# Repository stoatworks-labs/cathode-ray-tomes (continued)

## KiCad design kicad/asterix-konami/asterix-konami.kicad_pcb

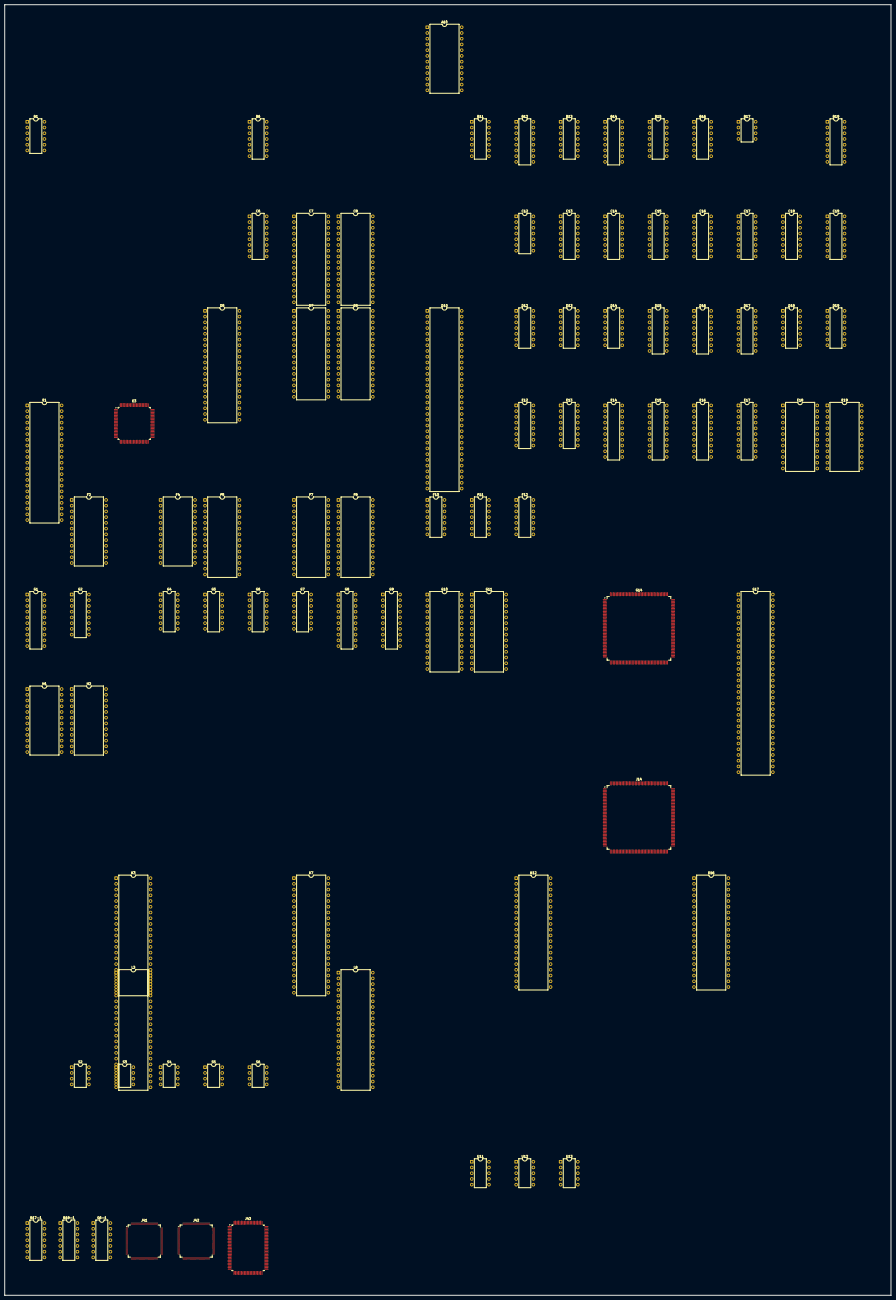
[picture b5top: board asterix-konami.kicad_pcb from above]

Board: 2 copper layers, 392.8 x 572.0 mm, 87 parts (0 on the bottom side), 556 nets, no tracks yet.

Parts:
A10: 051550; DIP-24_W15.24mm
B1: MB3722; DIP-12_W7.62mm
B6: LM324; DIP-14_W7.62mm
B11: 74LS74; DIP-14_W7.62mm
B12, B14: 74LS257; DIP-16_W7.62mm
B13: 74LS20; DIP-14_W7.62mm
B15, B16, B17-1, B18-1: 74LS07; DIP-14_W7.62mm
B17: ER5911; DIP-8_W7.62mm
B19: 74LS174; DIP-16_W7.62mm
C6: YM3012; DIP-16_W7.62mm
C7, C8: 27C010; DIP-32_W15.24mm
C12: 74LS74; DIP-14_W7.62mm
C13: 74LS139; DIP-16_W7.62mm
C14: 74LS138; DIP-16_W7.62mm
C15, C17: 74LS153; DIP-16_W7.62mm
C16: 74LS257; DIP-16_W7.62mm
C18, C19: 74LS174; DIP-16_W7.62mm
D5: Z80CPU; DIP-40_W15.24mm
D7, D8: 27C010; DIP-32_W15.24mm
D10: 68000D; DIP-64_W15.24mm
D12, D14: 74LS74; DIP-14_W7.62mm
D13: 74LS04; DIP-14_W7.62mm
D15, D17: 74LS157; DIP-16_W7.62mm
D16: 74LS257; DIP-16_W7.62mm
D18: 74LS32; DIP-14_W7.62mm
D19: 74LS164; DIP-14_W7.62mm
E1: DIP-42_W15.24mm
E3: 053260; PQFP-80_14x14mm_P0.65mm
E12: 74LS138; DIP-16_W7.62mm
E13: 74LS157; DIP-16_W7.62mm
E14, E17: 74LS245; DIP-20_W7.62mm
E15, E16: 74LS273; DIP-20_W7.62mm
E18, E19: HM6116P-3; DIP-24_W15.24mm
F2: CY7C128-45PC; DIP-24_W15.24mm
F4: YM2151; DIP-24_W15.24mm
F5: 27C512; DIP-28_W15.24mm
F7, F8: MB8464A-10W-15W; DIP-28_W15.24mm
F10: 74LS04; DIP-14_W7.62mm
F11: 74LS00; DIP-14_W7.62mm
F12: 74LS74; DIP-14_W7.62mm
G1: PAL16L8; DIP-20_W7.62mm
G2: 74LS161; DIP-16_W7.62mm
G4: 74LS04; DIP-14_W7.62mm
G5: 74LS00; DIP-14_W7.62mm
G6: 74LS74; DIP-14_W7.62mm
G6-1, G7: 74LS08; DIP-14_W7.62mm
G8, G9: 74LS245; DIP-20_W7.62mm
G10, G11: MB8464A-10W-15W; DIP-28_W15.24mm
G14: 054156; PQFP-160_28x28mm_P0.65mm
G17: DIP-64_W15.24mm
H1, H2: HM6116P-3; DIP-24_W15.24mm
J14: 054157; PQFP-160_28x28mm_P0.65mm
J41: 053245; TQFP-120_14x14mm_P0.4mm
J42: 053244; TQFP-120_14x14mm_P0.4mm
J43: 053251; PQFP-100_14x20mm_P0.65mm
K3, K7: DIP-42_W15.24mm
K12, K16: 955D05-06-07-08; DIP-40_W15.24mm
L3, L8: DIP-42_W15.24mm
S2, S3, S4, S5, S6: KONAMI_005273; DIP-8_W7.62mm
U11, U12, U13: 052535; DIP-10_W7.62mm

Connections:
/+12V: A10.19, B1.10
/ACOL0: J14.149, J43.57
/ACOL1: J14.148, J43.58
/ACOL2: J14.55, J43.59
/ACOL3: J14.56, J43.60
/APAL0: J14.127, J43.61
/APAL1: J14.126, J43.62
/APAL2: J14.125, J43.63
/AUX1: E3.23, F4.21
/BCOL0: J14.147, J43.66
/BCOL1: J14.146, J43.67
/BCOL2: J14.57, J43.68
/BCOL3: J14.58, J43.69
/BNK~CS: C14.11, C18.9, C19.9
/BNK~SCR: C14.7, J14.64
/BPAL0: J14.119, J43.70
/BPAL1: J14.118, J43.71
/BPAL2: J14.117, J43.72
/CI0: J14.154, J43.4
/CI1: J14.153, J43.5
/CI2: J14.51, J43.6
/CI3: J14.52, J43.7
/CI4: J14.142, J43.8
/CI5: J14.141, J43.9
/CI6: J14.138, J43.10
/COIN_CNT_1: A10.22, A10.23
/COIN_CNT_2: A10.20, A10.21
/CPG~CS: C14.10, J43.81
/FCOL0: J14.152, J43.47
/FCOL1: J14.151, J43.48
/FCOL2: J14.53, J43.49
/FCOL3: J14.54, J43.50
/FPAL0: J14.134, J43.51
/FPAL1: J14.133, J43.52
/FPAL2: J14.132, J43.54
/GFXROMA17: B19.15, K12.1, K16.1
/IO': B19.9, C14.14
/IO~OE: B12.15, B14.15, C14.15, C16.15, D16.15
/M3: C12.2, D14.11, G14.125
/M6: C12.3, D12.3, D12.11, D19.8, E15.11, E16.11, F12.12, G4.4, J43.41
/M12: B11.9, D10.15, G14.122, G17.56, J14.111
/MAIN_A1: C7.12, C8.12, D7.12, D8.12, D10.29, D15.2, D18.1, E3.18, F7.10, F8.10, G14.95, G17.30, J14.74, J41.25, J42.19, J43.85
/MAIN_A2: C7.11, C8.11, D7.11, D8.11, D10.30, D15.5, F7.9, F8.9, G14.96, G17.29, J14.75, J41.24, J42.18, J43.84
/MAIN_A3: C7.10, C8.10, D7.10, D8.10, D10.31, D15.11, F7.8, F8.8, G14.97, G17.28, J41.23, J42.17, J43.83
/MAIN_A4: C7.9, C8.9, D7.9, D8.9, D10.32, D15.14, F7.7, F8.7, G14.98, G17.27, J41.22, J42.15, J43.82
/MAIN_A5: C7.8, C8.8, D7.8, D8.8, D10.33, E13.2, F7.6, F8.6, G14.99, G17.24, J41.20
/MAIN_A6: C7.7, C8.7, D7.7, D8.7, D10.34, E13.5, F7.5, F8.5, G14.101, G17.23, J41.19
/MAIN_A7: C7.6, C8.6, D7.6, D8.6, D10.35, E13.11, F7.4, F8.4, G14.102, G17.22, J41.18
/MAIN_A8: C7.5, C8.5, C14.1, D7.5, D8.5, D10.36, E13.14, F7.3, F8.3, G14.103, G17.21, J41.17
/MAIN_A9: C7.27, C8.27, C14.2, D7.27, D8.27, D10.37, D17.2, F7.25, F8.25, G14.104, G17.20, J41.15
/MAIN_A10: C7.26, C8.26, C14.3, D7.26, D8.26, D10.38, D17.5, F7.24, F8.24, G14.105, G17.19, J41.14
/MAIN_A11: C7.23, C8.23, C14.4, D7.23, D8.23, D10.39, D17.11, F7.21, F8.21, G6-1.1, G7.1, G14.106, G17.17
/MAIN_A12: C7.25, C8.25, D7.25, D8.25, D10.40, F7.23, F8.23, G14.107, G17.16
/MAIN_A13: C7.4, C8.4, D7.4, D8.4, D10.41, F7.2, F8.2, G14.108, G17.15
/MAIN_A14: C7.28, C8.28, D7.28, D8.28, D10.42, F7.26, F8.26, G17.14
/MAIN_A15: C7.29, C8.29, D7.29, D8.29, D10.43, G17.13
/MAIN_A16: C7.3, C8.3, D7.3, D8.3, D10.44, G17.12
/MAIN_A17: C7.2, C8.2, C13.2, D7.2, D8.2, D10.45, G17.11
/MAIN_A18: C13.3, D10.46, G17.8
/MAIN_A19: D10.47, E12.1, G17.7
/MAIN_A20: D10.48, E12.2, G17.6
/MAIN_A21: D10.50, G17.5
/MAIN_A22: C13.14, D10.51, D13.11, E12.3, G17.4
/MAIN_A23: C13.13, D10.52, E12.4, G17.3
/MAIN_D0: B12.4, B19.3, C19.3, D7.13, D8.13, D10.5, E3.8, E17.2, F8.11, G8.18, G14.76, G17.31, J14.76, J42.29, J43.80
/MAIN_D1: B12.7, B19.4, C19.4, D7.14, D8.14, D10.4, E3.9, E17.3, F8.12, G8.17, G14.77, G17.32, J14.77, J42.28, J43.79
/MAIN_D2: B12.9, B19.6, C19.6, D7.15, D8.15, D10.3, E3.10, E17.4, F8.13, G8.16, G14.78, G17.33, J14.78, J42.27, J43.77
/MAIN_D3: B12.12, B19.11, C19.11, D7.17, D8.17, D10.2, E3.11, E17.5, F8.15, G8.15, G14.79, G17.35, J14.79, J42.26, J43.76
/MAIN_D4: B14.4, B19.13, C19.13, D7.18, D8.18, D10.1, E3.13, E17.6, F8.16, G8.14, G14.82, G17.36, J14.82, J42.25, J43.75
/MAIN_D5: B14.7, B19.14, C19.14, D7.19, D8.19, D10.64, E3.14, E17.7, F8.17, G8.13, G14.83, G17.37, J14.83, J42.24, J43.74
/MAIN_D6: B14.9, C18.3, D7.20, D8.20, D10.63, E3.15, E17.8, F8.18, G8.12, G14.84, G17.38, J14.84, J42.23
/MAIN_D7: B14.12, C18.4, D7.21, D8.21, D10.62, E3.16, E17.9, F8.19, G8.11, G14.85, G17.39, J14.85, J42.22
/MAIN_D8: C7.13, C8.13, C16.4, C18.6, D10.61, E14.2, F7.11, G9.18, G14.86, G17.40, J14.86
/MAIN_D9: C7.14, C8.14, C16.7, C18.11, D10.60, E14.3, F7.12, G9.17, G14.87, G17.43, J14.87
/MAIN_D10: C7.15, C8.15, C16.9, C18.13, D10.59, E14.4, F7.13, G9.16, G14.88, G17.44, J14.88
/MAIN_D11: C7.17, C8.17, C16.12, C18.14, D10.58, E14.5, F7.15, G9.15, G14.89, G17.45, J14.89
/MAIN_D12: C7.18, C8.18, D10.57, D16.4, E14.6, F7.16, G9.14, G14.91, G17.46, J14.91
/MAIN_D13: C7.19, C8.19, D10.56, D16.7, E14.7, F7.17, G9.13, G14.92, G17.47, J14.92
/MAIN_D14: C7.20, C8.20, D10.55, D16.9, E14.8, F7.18, G9.12, G14.93, G17.48, J14.93
/MAIN_D15: C7.21, C8.21, D10.54, D16.12, E14.9, F7.19, G9.11, G14.94, G17.49, J14.94
/MRESET: A10.1, C14.9
/M~DS: D13.1, G6-1.6, J42.14
/M~RD: C7.22, C8.22, D7.22, D8.22, D17.14, E14.1, E17.1, F7.22, F8.22, F11.1, F11.13, G4.10, J41.13, J42.20
/OBJ~CE: F11.6, G5.1
/OBJ~CS: D18.5, E12.12, F11.4
/OBJ~RD: E12.11, F11.5, G7.5
/OBJ~SET: E12.9, J41.6, J42.13
/OCOL0: J42.120, J43.30
/OCOL1: J42.119, J43.31
/OCOL2: J42.118, J43.32
/OCOL3: J42.117, J43.33
/OCOL4: J42.116, J43.34
/OCOL5: J42.115, J43.35
/OCOL6: J42.114, J43.36
/OCOL7: J42.113, J43.37
/OCOL8: J42.112, J43.38
/PAL~CS: D15.1, D17.1, D18.10, D18.13, E12.10, E13.1, E14.19, E17.19
/PCMCLK: E3.21, F4.24, G2.12
/PCM~CS: E3.72, G1.19
/PR13: J42.110, J43.25
/PR14: J42.109, J43.27
/R/~W: D10.9, D18.4, E3.19, G4.11
/SDI0: J42.108, J43.95
/SH1: C6.6, E3.26, G6.11
/SND_A0: D5.30, E3.70, F2.8, F4.4, F5.10
/SND_A1: D5.31, E3.69, F2.7, F5.9
/SND_A2: D5.32, E3.68, F2.6, F5.8
/SND_A3: D5.33, E3.67, F2.5, F5.7
/SND_A4: D5.34, E3.66, F2.4, F5.6
/SND_A5: D5.35, E3.65, F2.3, F5.5
/SND_A6: D5.36, F2.2, F5.4
/SND_A7: D5.37, F2.1, F5.3
/SND_A8: D5.38, F2.23, F5.25
/SND_A9: D5.39, F2.22, F5.24, G1.14
/SND_A10: D5.40, F2.19, F5.21, G1.13
/SND_A11: D5.1, F5.23, G1.11
/SND_A12: D5.2, F5.2, G1.9
/SND_A13: D5.3, F5.26, G1.8
/SND_A14: D5.4, F5.27, G1.7
/SND_A15: D5.5, F5.1, G1.6
/SND_D0: D5.14, E3.5, F2.9, F4.10, F5.11
/SND_D1: D5.15, E3.4, F2.10, F4.12, F5.12
/SND_D2: D5.12, E3.3, F2.11, F4.13, F5.13
/SND_D3: D5.8, E3.2, F2.13, F4.14, F5.15
/SND_D4: D5.7, E3.1, F2.14, F4.15, F5.16
/SND_D5: D5.9, E3.80, F2.15, F4.16, F5.17
/SND_D6: D5.10, E3.79, F2.16, F4.17, F5.18
/SND_D7: D5.13, E3.78, F2.17, F4.18, F5.19
/STBI: E3.22, F4.20
/S~RD: D5.21, F2.20, F4.6, F10.13, G1.4
/TMG2TD0: G14.64, J14.62
/TMG2TD1: G14.109, J14.68
/TMG2TD2: G14.124, J14.69
/TMG2TD3: G14.126, J14.72
/TMG2TD4: G14.127, J14.73
/TMG2TD5: G14.128, J14.95
/TMG2TD6: G14.129, J14.98
/TMG2TD7: D13.4, G14.62, J14.112
/colmix/CO0: D15.3, J43.19
/colmix/CO1: D15.6, J43.18
/colmix/CO2: D15.10, J43.17
/colmix/CO3: D15.13, J43.16
/colmix/CO4: E13.3, J43.14
/colmix/CO5: E13.6, J43.13
/colmix/CO6: E13.10, J43.12
/colmix/CO7: E13.13, J43.11
/colmix/CO8: D17.3, J43.93
/colmix/CO9: D17.6, J43.92
/colmix/CO10: D17.10, J43.91
/colmix/MCO0: D15.4, E18.8, E19.8
/colmix/MCO1: D15.7, E18.7, E19.7
/colmix/MCO2: D15.9, E18.6, E19.6
/colmix/MCO3: D15.12, E18.5, E19.5
/colmix/MCO4: E13.4, E18.4, E19.4
/colmix/MCO5: E13.7, E18.3, E19.3
/colmix/MCO6: E13.9, E18.2, E19.2
/colmix/MCO7: E13.12, E18.1, E19.1
/colmix/MCO8: D17.4, E18.23, E19.23
/colmix/MCO9: D17.7, E18.22, E19.22
/colmix/MCO10: D17.9, E18.19, E19.19
/colmix/MCO~OE: D17.12, E18.20, E19.20
/colmix/MCO~WRH: D18.8, E19.21
/colmix/MCO~WRL: D18.11, E18.21
/colmix/RGB0: E15.4, E17.18, E18.9
/colmix/RGB1: E15.7, E17.17, E18.10
/colmix/RGB2: E15.8, E17.16, E18.11
/colmix/RGB3: E15.13, E17.15, E18.13
/colmix/RGB4: E15.14, E17.14, E18.14
/colmix/RGB5: E15.17, E17.13, E18.15
/colmix/RGB6: E15.18, E17.12, E18.16
/colmix/RGB7: E16.3, E17.11, E18.17
/colmix/RGB8: E14.18, E16.4, E19.9
/colmix/RGB9: E14.17, E16.7, E19.10
/colmix/RGB10: E14.16, E16.8, E19.11
/colmix/RGB11: E14.15, E16.13, E19.13
/colmix/RGB12: E14.14, E16.14, E19.14
/colmix/RGB13: E14.13, E16.17, E19.15
/colmix/RGB14: E14.12, E16.18, E19.16
/colmix/RGB15: E14.11, E19.17
/colmix/SDO1: D13.5, J43.86
/colmix/rgb/B10: B15.3, E16.9
/colmix/rgb/B11: B17-1.9, E16.12
/colmix/rgb/B12: B15.5, E16.15
/colmix/rgb/B13: B17-1.11, E16.16
/colmix/rgb/B14: B18-1.9, E16.19
/colmix/rgb/G5: B16.3, E15.16
/colmix/rgb/G6: B17-1.13, E15.19
/colmix/rgb/G7: B16.5, E16.2
/colmix/rgb/G8: B17-1.3, E16.5
/colmix/rgb/G9: B15.1, E16.6
/colmix/rgb/R0: B16.9, E15.5
/colmix/rgb/R1: B15.9, E15.6
/colmix/rgb/R2: B16.11, E15.9
/colmix/rgb/R3: B15.11, E15.12
/colmix/rgb/R4: B16.13, E15.15
/colmix/rgb/~SHADOW: B15.13, B18-1.5, B18-1.13, E15.2
/io_cabinet/I1P_BTN_1: B14.2, S5.3
/io_cabinet/I1P_BTN_2: B14.5, S6.7
/io_cabinet/I1P_BTN_3: B14.11, S6.3
/io_cabinet/I1P_DOWN: B12.14, S4.7
/io_cabinet/I1P_LEFT: B12.2, S4.3
/io_cabinet/I1P_RIGHT: B12.5, S5.7
/io_cabinet/I1P_START: B14.14, S3.7
/io_cabinet/I1P_UP: B12.11, S3.3
/io_cabinet/I2P_BTN_1: B14.3, S5.1
/io_cabinet/I2P_BTN_2: B14.6, S6.5
/io_cabinet/I2P_BTN_3: B14.10, S6.1
/io_cabinet/I2P_DOWN: B12.13, S4.5
/io_cabinet/I2P_LEFT: B12.3, S4.1
/io_cabinet/I2P_RIGHT: B12.6, S5.5
/io_cabinet/I2P_START: B14.13, S3.5
/io_cabinet/I2P_UP: B12.10, S3.1
/io_cabinet/ICOIN_1: C16.2, S2.3
/io_cabinet/ICOIN_2: C16.5, S2.1
/io_cabinet/ISERVICE1: C16.11, S2.7
/io_cabinet/ITEST SW1: C16.10, S2.5
/io_cabinet/~M12: B11.8, B11.12, C12.11, F12.2
/main/AS: B13.9, D12.4, D12.10, D14.4, D14.10, G4.2
/main/~AS: C13.15, D10.6, E12.5, G4.1, G17.1
/main/~BGACK: D10.12, G17.53
/main/~BG: D10.11, G17.52
/main/~BR: D10.13, G17.51
/main/~CS1: E12.13, F7.20, F8.20
/main/~DTACK: D10.10, D13.12, G17.61
/main/~IO: C14.5, E12.7, F10.1
/main/~OE1: C8.24, D8.24, E12.15
/main/~OE2: C7.24, D7.24, E12.14
/objects/AR0: J41.119, J42.30
/objects/AR1: J41.118, J42.32
/objects/AR2: J41.117, J42.33
/objects/AROK: J41.116, J42.34
/objects/BR0: J41.115, J42.35
/objects/BR1: J41.114, J42.36
/objects/BR2: J41.113, J42.37
/objects/BROK: J41.112, J42.38
/objects/CLAT: J41.86, J42.64
/objects/CPU: F10.10, G5.2, G7.2
/objects/HP0: J41.96, J42.54
/objects/HP1: J41.97, J42.53
/objects/HP2: J41.98, J42.52
/objects/HP3: J41.99, J42.50
/objects/HP4: J41.100, J42.49
/objects/HP5: J41.102, J42.48
/objects/HP6: J41.103, J42.47
/objects/HP7: J41.104, J42.45
/objects/HP8: J41.105, J42.44
/objects/HP9: J41.107, J42.43
/objects/HRFP: J41.110, J42.39
/objects/MA11: G7.3, H1.19, H2.19
/objects/MAIN_D'0: C17.2, C17.6, C17.14, C19.2, J41.64, J41.65, J41.66, J41.67, J41.68, J41.69, J41.70, J41.85, K3.10, K3.33, K3.34, K3.35, K3.36, K3.37, K7.10, K7.33, K7.34, K7.35, K7.36, K7.37, L3.10, L3.33, L3.34, L3.35, L3.36, L3.37, L8.10, L8.33, L8.34, L8.35, L8.36, L8.37
/objects/MAIN_D'1: C17.10, C19.5, J41.84, K3.9, K7.9, L3.9, L8.9
/objects/MAIN_D'2: C15.6, C19.7, J41.83, K3.8, K7.8, L3.8, L8.8
/objects/MAIN_D'3: C17.5, C19.10, J41.82, K3.7, K7.7, L3.7, L8.7
/objects/MAIN_D'4: C17.11, C19.12, J41.80, K3.6, K7.6, L3.6, L8.6
/objects/MAIN_D'5: C15.5, C19.15, J41.79, K3.5, K7.5, L3.5, L8.5
/objects/MAIN_D'6: C17.4, C18.2, J41.78, K3.4, K7.4, L3.4, L8.4
/objects/MAIN_D'7: C17.12, C18.5, J41.77, K3.3, K7.3, L3.3, L8.3
/objects/MAIN_D'8: C15.4, C18.7, J41.75, K3.41, K7.41, L3.41, L8.41
/objects/MAIN_D'9: C17.3, C18.10, J41.74, K3.40, K7.40, L3.40, L8.40
/objects/MAIN_D'10: C17.13, C18.12, J41.73, K3.39, K7.39, L3.39, L8.39
/objects/MAIN_D'11: C15.3, C18.15, J41.72, K3.38, K7.38, L3.38, L8.38
/objects/MAIN_D'[11..0]: C15.2, C15.14
/objects/OBJROMD0: J42.100, K7.14, L3.14
/objects/OBJROMD1: J42.99, K7.16, L3.16
/objects/OBJROMD2: J42.98, K7.18, L3.18
/objects/OBJROMD3: J42.97, K7.20, L3.20
/objects/OBJROMD4: J42.96, K7.23, L3.23
/objects/OBJROMD5: J42.95, K7.25, L3.25
/objects/OBJROMD6: J42.94, K7.27, L3.27
/objects/OBJROMD7: J42.93, K7.29, L3.29
/objects/OBJROMD8: J42.92, K7.15, L3.15
/objects/OBJROMD9: J42.90, K7.17, L3.17
/objects/OBJROMD10: J42.89, K7.19, L3.19
/objects/OBJROMD11: J42.88, K7.21, L3.21
/objects/OBJROMD12: J42.87, K7.24, L3.24
/objects/OBJROMD13: J42.86, K7.26, L3.26
/objects/OBJROMD14: J42.85, K7.28, L3.28
/objects/OBJROMD15: J42.84, K7.30, L3.30
/objects/OBJROMD16: J42.83, K3.14, L8.14
/objects/OBJROMD17: J42.82, K3.16, L8.16
/objects/OBJROMD18: J42.80, K3.18, L8.18
/objects/OBJROMD19: J42.79, K3.20, L8.20
/objects/OBJROMD20: J42.78, K3.23, L8.23
/objects/OBJROMD21: J42.77, K3.25, L8.25
/objects/OBJROMD22: J42.75, K3.27, L8.27
/objects/OBJROMD23: J42.74, K3.29, L8.29
/objects/OBJROMD24: J42.73, K3.15, L8.15
/objects/OBJROMD25: J42.72, K3.17, L8.17
/objects/OBJROMD26: J42.70, K3.19, L8.19
/objects/OBJROMD27: J42.69, K3.21, L8.21
/objects/OBJROMD28: J42.68, K3.24, L8.24
/objects/OBJROMD29: J42.67, K3.26, L8.26
/objects/OBJROMD30: J42.66, K3.28, L8.28
/objects/OBJROMD31: J42.65, K3.30, L8.30
/objects/PL0: J41.87, J42.63
/objects/PL1: J41.88, J42.62
/objects/PL2: J41.89, J42.60
/objects/PL3: J41.90, J42.59
/objects/PL4: J41.92, J42.58
/objects/PL5: J41.93, J42.57
/objects/PL6: J41.94, J42.56
/objects/RA1: H1.8, H2.8, J41.52
/objects/RA2: H1.7, H2.7, J41.53
/objects/RA3: H1.6, H2.6, J41.54
/objects/RA4: H1.5, H2.5, J41.55
/objects/RA5: H1.4, H2.4, J41.56
/objects/RA6: H1.3, H2.3, J41.57
/objects/RA7: H1.2, H2.2, J41.58
/objects/RA8: H1.1, H2.1, J41.59
/objects/RA9: H1.23, H2.23, J41.62
/objects/RA10: H1.22, H2.22, J41.63
/objects/RD0: G8.2, H2.9, J41.45
/objects/RD1: G8.3, H2.10, J41.44
/objects/RD2: G8.4, H2.11, J41.43
/objects/RD3: G8.5, H2.13, J41.42
/objects/RD4: G8.6, H2.14, J41.40
/objects/RD5: G8.7, H2.15, J41.39
/objects/RD6: G8.8, H2.16, J41.38
/objects/RD7: G8.9, H2.17, J41.37
/objects/RD8: G9.2, H1.9, J41.35
/objects/RD9: G9.3, H1.10, J41.34
/objects/RD10: G9.4, H1.11, J41.33
/objects/RD11: G9.5, H1.13, J41.32
/objects/RD12: G9.6, H1.14, J41.30
/objects/RD13: G9.7, H1.15, J41.29
/objects/RD14: G9.8, H1.16, J41.28
/objects/RD15: G9.9, H1.17, J41.27
/objects/R~OE: H1.20, H2.20, J41.49
/objects/SHADOW: J41.95, J42.55
/objects/~HIT: J41.108, J42.42
/objects/~WE1: H2.21, J41.48
/objects/~WE2: H1.21, J41.47
/objects/~ZLD: J41.109, J42.40
/pcm/RA0: E1.30, E3.39
/pcm/RA1: E1.10, E3.40
/pcm/RA2: E1.9, E3.41
/pcm/RA3: E1.8, E3.42
/pcm/RA4: E1.7, E3.44
/pcm/RA5: E1.6, E3.45
/pcm/RA6: E1.5, E3.46
/pcm/RA7: E1.4, E3.47
/pcm/RA8: E1.3, E3.48
/pcm/RA9: E1.41, E3.49
/pcm/RA10: E1.40, E3.50
/pcm/RA11: E1.39, E3.51
/pcm/RA12: E1.38, E3.53
/pcm/RA13: E1.37, E3.54
/pcm/RA14: E1.36, E3.55
/pcm/RA15: E1.35, E3.56
/pcm/RA16: E1.34, E3.57
/pcm/RA17: E1.33, E3.58
/pcm/RA18: E1.2, E3.59
/pcm/RA19: E1.1, E3.60
/pcm/RA20: E1.42, E3.62
/pcm/RD0: E1.14, E3.29
/pcm/RD1: E1.16, E3.30
/pcm/RD2: E1.18, E3.31
/pcm/RD3: E1.20, E3.32
/pcm/RD4: E1.23, E3.35
/pcm/RD5: E1.25, E3.36
/pcm/RD6: E1.27, E3.37
/pcm/RD7: E1.29, E3.38
/pcm/SH2: C6.5, E3.27
/pcm/SY: C6.2, E3.25
/scroll/GFXROMA0: G14.159, K12.9, K16.9
/scroll/GFXROMA1: G14.158, K12.8, K16.8
/scroll/GFXROMA2: G14.157, K12.7, K16.7
/scroll/GFXROMA3: G14.156, K12.6, K16.6
/scroll/GFXROMA4: G14.155, K12.5, K16.5
/scroll/GFXROMA5: G14.154, K12.4, K16.4
/scroll/GFXROMA6: G14.153, K12.3, K16.3
/scroll/GFXROMA7: G14.152, K12.2, K16.2
/scroll/GFXROMA8: G14.151, K12.40, K16.40
/scroll/GFXROMA9: G14.149, K12.39, K16.39
/scroll/GFXROMA10: G14.148, K12.38, K16.38
/scroll/GFXROMA11: G14.134, K12.37, K16.37
/scroll/GFXROMA12: G14.133, K12.36, K16.36
/scroll/GFXROMA13: G14.137, K12.35, K16.35
/scroll/GFXROMA14: G14.132, K12.34, K16.34
/scroll/GFXROMA15: G14.131, K12.33, K16.33
/scroll/GFXROMA16: G14.136, K12.32, K16.32
/scroll/GFXROMD0: J14.44, K12.13
/scroll/GFXROMD1: J14.45, K12.15
/scroll/GFXROMD2: J14.46, J14.48, K12.17
/scroll/GFXROMD3: J14.47, J14.49, K12.19
/scroll/GFXROMD4: J14.36, K12.22
/scroll/GFXROMD5: J14.37, K12.24
/scroll/GFXROMD6: J14.38, J14.42, K12.26
/scroll/GFXROMD7: J14.39, J14.43, K12.28
/scroll/GFXROMD8: J14.29, K12.14
/scroll/GFXROMD9: J14.31, K12.16
/scroll/GFXROMD10: J14.32, J14.35, K12.18
/scroll/GFXROMD11: J14.33, J14.34, K12.20
/scroll/GFXROMD12: J14.23, K12.23
/scroll/GFXROMD13: J14.24, K12.25
/scroll/GFXROMD14: J14.25, J14.27, K12.27
/scroll/GFXROMD15: J14.26, J14.28, K12.29
/scroll/GFXROMD16: J14.16, K16.13
/scroll/GFXROMD17: J14.17, K16.15
/scroll/GFXROMD18: J14.18, J14.21, K16.17
/scroll/GFXROMD19: J14.19, J14.22, K16.19
/scroll/GFXROMD20: J14.9, K16.22
/scroll/GFXROMD21: J14.11, K16.24
/scroll/GFXROMD22: J14.12, J14.14, K16.26
/scroll/GFXROMD23: J14.13, J14.15, K16.28
/scroll/GFXROMD24: J14.3, K16.14
/scroll/GFXROMD25: J14.4, K16.16
/scroll/GFXROMD26: J14.5, J14.7, K16.18
/scroll/GFXROMD27: J14.6, J14.8, K16.20
/scroll/GFXROMD28: J14.155, K16.23
/scroll/GFXROMD29: J14.156, K16.25
/scroll/GFXROMD30: J14.157, K16.27
/scroll/GFXROMD31: J14.2, J14.158, K16.29
/scroll/SCRAMA0: G10.10, G11.10, G14.28
/scroll/SCRAMA1: G10.9, G11.9, G14.29
/scroll/SCRAMA2: G10.8, G11.8, G14.31
/scroll/SCRAMA3: G10.7, G11.7, G14.32
/scroll/SCRAMA4: G10.6, G11.6, G14.33
/scroll/SCRAMA5: G10.5, G11.5, G14.34
/scroll/SCRAMA6: G10.4, G11.4, G14.35
/scroll/SCRAMA7: G10.3, G11.3, G14.36
/scroll/SCRAMA8: G10.25, G11.25, G14.37
/scroll/SCRAMA9: G10.24, G11.24, G14.38
/scroll/SCRAMA10: G10.21, G11.21, G14.39
/scroll/SCRAMA11: G10.23, G11.23, G14.42
/scroll/SCRAMA12: G10.2, G11.2, G14.45
/scroll/VD0: G11.11, G14.9
/scroll/VD1: G11.12, G14.8
/scroll/VD2: G11.13, G14.7
/scroll/VD3: G11.15, G14.6
/scroll/VD4: G11.16, G14.5
/scroll/VD5: G11.17, G14.4
/scroll/VD6: G11.18, G14.3
/scroll/VD7: G11.19, G14.2
/scroll/VD8: G10.11, G14.27
/scroll/VD9: G10.12, G14.26
/scroll/VD10: G10.13, G14.25
/scroll/VD11: G10.15, G14.24
/scroll/VD12: G10.16, G14.23
/scroll/VD13: G10.17, G14.22
/scroll/VD14: G10.18, G14.21
/scroll/VD15: G10.19, G14.19
/scroll/~M6: G4.3, G14.111
/scroll/~RCS1: G11.20, G14.52
/scroll/~RCS2: G10.20, G14.48
/scroll/~ROE1: G11.22, G14.53
/scroll/~ROE2: G10.22, G14.49
/scroll/~RWE1: G11.27, G14.54
/scroll/~RWE2: G10.27, G14.51
/sound/ROM~OE: F5.22, G1.16
/sound/SRAM~CE: F2.18, G1.17
/sound/S~IORQ: D5.20, G6-1.12
/sound/S~MREQ: D5.19, G1.2
/sound/S~WR: D5.22, F2.21, F4.5, G1.5
/sound/~M1: D5.27, G1.3
/sound/~NMISET: G1.12, G6.10
/sound/~RFSH: D5.28, G1.1
/sound/~WSET: B11.4, G1.15
/~CLKTMG: D14.5, D14.12, G14.112
/~CLKTMG~M6: F12.9, J41.10, J42.10
/~CLKTMG~M12: F12.5, J41.12, J42.12
/~CPU: C16.13, F10.11, J41.26
/~HBLANK: D19.2, G14.116
/~HSYNC: G6-1.10, G14.114, J41.4, J42.8
/~IPL0: D10.25, D16.6, G17.60
/~IPL2: D10.23, G14.72
/~LDS: D10.8, F10.5, G6-1.5, G17.63, J14.96, J41.9
/~MCS: C14.13, E3.17
/~RESET: G7.4, G17.64
/~SOUND: C14.12, G6.3
/~SYSRES: B18-1.3, B18-1.11, C6.7, C12.9, D5.26, D19.9, E3.75, F4.3, G6.13, G6-1.13, G14.71, G17.59, J14.109, J41.3, J42.3
/~UDS: D10.7, F10.3, G6-1.4, G17.62, J14.97, J41.8
/~VBLANK: D16.3, D19.1, G14.117
/~VSYNC: G6-1.9, G14.115, J41.5, J42.9
/~WEH: D18.9, F7.27, F11.11
/~WEL: D18.12, F8.27, F11.3
GND: C7.16, C8.16, D7.16, D8.16, D10.16, D10.53, F5.14, F5.20, G1.10
unnamed: A10.15, B19.10
unnamed: A10.16, B19.12
unnamed: A10.10, C12.12, C12.13
unnamed: B6.3, C6.9
unnamed: B6.1, B6.2
unnamed: B6.5, C6.15
unnamed: B6.6, C6.14
unnamed: B6.10, C6.12
unnamed: B6.8, B6.9
unnamed: B6.12, C6.10
unnamed: B6.13, B6.14
unnamed: B11.3, D5.6, G2.13
unnamed: B11.2, B11.6
unnamed: B11.11, F12.3, F12.11
unnamed: B12.1, B14.1, C16.1, D16.1, D18.3
unnamed: B13.6, D13.13
unnamed: B16.1, G6-1.8
unnamed: B17.2, B19.7
unnamed: B17.1, B19.5
unnamed: B17.3, B19.2
unnamed: B17.4, C16.3
unnamed: B17.7, C16.6
unnamed: B6.7, C6.13
unnamed: C12.6, D14.3
unnamed: C13.1, C13.11
unnamed: C13.4, D14.2
unnamed: C13.5, D12.12, D13.3
unnamed: B13.2, C13.6
unnamed: B13.4, C13.12
unnamed: C14.6, D13.2, G6-1.2
unnamed: C15.7, F10.9
unnamed: C17.7, K3.2, K7.2, L3.2, L8.2
unnamed: C17.9, K3.1, K7.1, L3.1, L8.1
unnamed: D5.16, G6.6
unnamed: D5.17, G6.9
unnamed: B13.10, D10.28
unnamed: B13.12, D10.27
unnamed: B13.13, D10.26
unnamed: B18-1.4, D10.17
unnamed: B18-1.10, D10.18
unnamed: B13.8, D10.21
unnamed: D12.2, D12.9
unnamed: B13.1, D12.5
unnamed: B13.5, D14.9
unnamed: B17-1.1, B17-1.5, B18-1.1, D19.3
unnamed: E3.71, F10.12
unnamed: D13.10, E12.6
unnamed: D13.6, E15.3
unnamed: F4.7, G1.18
unnamed: F10.2, F11.10
unnamed: F10.4, F11.12
unnamed: F10.6, F11.2
unnamed: F11.9, G6-1.3
unnamed: G6.1, G6-1.11
unnamed: G7.6, G8.1, G9.1
unnamed: G5.3, G8.19, G9.19
unnamed: F11.8, G17.54
unnamed: D18.6, J41.7
unnamed: F10.8, L3.13
unnamed: B18-1.2, U11.7
unnamed: B15.4, U11.6
unnamed: B17-1.8, U11.5
unnamed: B15.6, U11.4
unnamed: B17-1.10, U11.3
unnamed: B18-1.8, U11.2
unnamed: B17-1.6, U12.7
unnamed: B16.4, U12.6
unnamed: B17-1.12, U12.5
unnamed: B16.6, U12.4
unnamed: B17-1.4, U12.3
unnamed: B15.2, U12.2
unnamed: B17-1.2, U13.7
unnamed: B16.8, U13.6
unnamed: B15.8, U13.5
unnamed: B16.10, U13.4
unnamed: B15.10, U13.3
unnamed: B16.12, U13.2
VCC: A10.9, B6.4, B11.1, B11.10, B11.13, B11.14, B13.14, B15.14, B16.14, B17.8, B17-1.14, B18-1.14, B19.1, C6.1, C7.1, C7.31, C7.32, C8.1, C8.31, C8.32, C12.1, C12.4, C12.10, C12.14, C13.16, C16.14, C18.1, C19.1, D5.11, D7.1, D7.31, D7.32, D8.1, D8.31, D8.32, D10.14, D10.24, D10.49, D12.1, D12.13, D12.14, D13.14, D14.1, D14.13, D14.14, D16.2, D16.5, D16.10, D16.11, D16.13, D16.14, D18.14, D19.14, E1.22, E1.31, E3.20, E3.33, E3.73, E15.1, E16.1, E18.24, E19.24, F2.24, F4.22, F5.28, F7.28, F8.28, F10.14, F11.14, F12.1, F12.4, F12.10, F12.13, F12.14, G1.20, G2.1, G2.7, G2.9, G2.10, G4.14, G5.14, G6.2, G6.4, G6.14, G6-1.14, G7.14, G10.26, G10.28, G11.26, G11.28, G14.20, G14.40, G14.60, G14.80, G14.100, G14.118, G14.119, G14.120, G14.140, G14.160, G17.9, G17.26, G17.41, G17.58, H1.24, H2.24, J14.20, J14.40, J14.60, J14.65, J14.66, J14.67, J14.71, J14.80, J14.100, J14.106, J14.107, J14.108, J14.113, J14.116, J14.120, J14.122, J14.123, J14.124, J14.128, J14.129, J14.131, J14.135, J14.140, J14.159, J14.160, J41.16, J41.46, J41.60, J41.76, J41.106, J41.120, J42.16, J42.46, J42.76, J42.106, J43.1, J43.2, J43.3, J43.28, J43.29, J43.39, J43.42, J43.43, J43.44, J43.45, J43.46, J43.53, J43.78, J43.97, J43.98, J43.99, J43.100, K3.22, K3.31, K3.32, K7.22, K7.31, K7.32, K12.21, K12.31, K16.21, K16.31, L3.22, L3.31, L3.32, L8.22, L8.31, L8.32, U11.1, U12.1, U13.1
VSS: A10.13, A10.14, B1.6, B1.7, B6.11, B11.7, B13.7, B15.7, B16.7, B17.5, B17.6, B17-1.7, B18-1.7, C6.3, C6.8, C6.16, C12.7, C13.8, C15.1, C15.10, C15.11, C15.12, C15.13, C15.15, C17.1, C17.15, D5.29, D12.7, D13.7, D14.7, D15.15, D17.13, D17.15, D18.2, D18.7, D19.7, E1.11, E1.12, E1.13, E1.32, E3.6, E3.12, E3.24, E3.34, E3.43, E3.52, E3.61, E3.74, E13.15, E18.12, E18.18, E19.12, E19.18, F2.12, F4.1, F4.11, F7.14, F8.14, F10.7, F11.7, F12.7, G2.3, G2.4, G2.5, G2.6, G4.7, G5.7, G6.7, G6.12, G6-1.7, G7.7, G10.14, G11.14, G14.1, G14.10, G14.30, G14.41, G14.50, G14.59, G14.70, G14.81, G14.90, G14.110, G14.121, G14.130, G14.135, G14.139, G14.150, G17.2, G17.10, G17.18, G17.25, G17.34, G17.42, G17.50, G17.55, G17.57, H1.12, H1.18, H2.12, H2.18, J14.1, J14.10, J14.30, J14.41, J14.50, J14.59, J14.70, J14.81, J14.90, J14.110, J14.121, J14.130, J14.139, J14.150, J41.1, J41.2, J41.11, J41.21, J41.31, J41.41, J41.51, J41.61, J41.71, J41.81, J41.91, J41.101, J41.111, J42.1, J42.2, J42.11, J42.21, J42.31, J42.41, J42.51, J42.61, J42.71, J42.81, J42.91, J42.101, J42.111, J43.15, J43.20, J43.21, J43.22, J43.23, J43.24, J43.40, J43.55, J43.56, J43.64, J43.65, J43.73, J43.90, J43.94, K3.11, K3.12, K3.13, K7.11, K7.12, K7.13, K12.10, K12.11, K12.12, K12.30, K16.10, K16.11, K16.12, K16.30, L3.11, L3.12, L8.11, L8.12, L8.13, U11.9, U12.9, U13.9

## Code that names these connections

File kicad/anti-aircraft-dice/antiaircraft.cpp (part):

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    * Signals                                                                 *
	**************************************************************************/
	#define CLOCK  "J4", 9
	#define CLOCK_n  "J4", 8

    #define H1 "H4", 14
    #define H2 "H4", 13
    #define H4 "H4", 12
    #define H8 "H4", 11
    #define H16 "H5", 14
    #define H16_n "K3", 6
    #define H32 "H5", 13
    #define H64 "H5", 12
    #define H64_n "K3", 4
    #define H128 "H5", 11
    #define H256 "J6", 3
    #define H256_n "J6", 2

    #define H256_xor_H32 "C6", 3
    #define H128_xor_H256 "C6", 8
    #define H128_xor_H256_n "C8", 12

    #define HRESET "J4", 6
    #define HRESET_n "J4", 5

    #define HSYNC "J3", 4
    #define HSYNC_n "J3", 1

    #define V1 "K4", 12
    #define V2 "K4", 9
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    #define V64 "K5", 8
    #define V128 "K5", 11
    #define V256 "J6", 5
    #define V256_n "J6", 6

    #define V1_n "K3", 2
    #define V2_n "K3", 8
    #define V4_n "K3", 10
    #define V8_n "K3", 12

    #define VRESET "J5", 6
    #define VRESET_n "J5", 5

    #define VSYNC "J3", 10
    #define VSYNC_n "J3", 13

    #define COMP_SYNC "J2", 3

    #define SCOREV_n "C7", 6

    #define Q "F9", 10

    #define ATTRACT "D8", 9
    #define ATTRACT_n "D8", 8

    #define RA "K9", 5
    #define RB "K9", 9
    #define RA_n "K9", 6
    #define RB_n "K9", 8

    #define RA_nor_RB "N6", 10

    #define LA "K8", 5
    #define LB "K8", 9
    #define LA_n "K8", 6
    #define LB_n "K8", 8

    #define LA_or_LB "N4", 10

    #define FIRE_RIGHT "J8", 6
    #define FIRE_RIGHT_n "J8", 5

    #define FIRE_LEFT "J8", 8
    #define FIRE_LEFT_n "J8", 9

    #define RMH1 "M8", 14
    #define RMH2 "M8", 13
    #define RMH3 "M8", 12
    #define RMH4 "M8", 11

    #define RMV1 "L7", 14
    #define RMV2 "L7", 13
    #define RMV3 "L7", 12
    #define RMV4 "L7", 11

    #define LARGE_RIGHT_MISSILE "N9", 10
    #define RIGHT_MISSILE_n "M9", 11
    #define RIGHT_MISSILE_WIN "L6", 4

    #define LMH1 "E6", 14
    #define LMH2 "E6", 13
    #define LMH3 "E6", 12
    #define LMH4 "E6", 11

    #define LMV1 "D6", 14
    #define LMV2 "D6", 13
    #define LMV3 "D6", 12
    #define LMV4 "D6", 11

    #define LARGE_LEFT_MISSILE "C3", 4
    #define LEFT_MISSILE_n "F4", 8
    #define LEFT_MISSILE_WIN "F3", 13

    #define RT_HIT "B1", 6
    #define RT_HIT_n "B1", 7

    #define LT_HIT "B1", 10
    #define LT_HIT_n "B1", 9

    #define DELAY_R "C1", 6
    #define DELAY_L "C1", 10

    #define FLASH "A3", 8

    #define MISSILE_VRESET "F5", 8
    #define VCOUNT_n "F4", 11

    #define PLANE_RESET "K2", 8 
    #define PLANE_RESET_n "K2", 9

    #define PH1 "H1", 14
    #define PH2 "H1", 13
    #define PH3 "H1", 12
    #define PH4 "H1", 11

    #define DIR_SELECT_n "F2", 3

    #define RANDOM_CLOCK "D3", 8

    #define START "D8", 5
    #define START_n "D8", 6

    #define HIT_DETECT "B2", 6
    #define TARGET_HIT_n "B3", 8

    #define COMP_HIT_n "C2", 6

    #define VPLANE_ENABLE "E2", 4
    #define PLANE_EN "H2", 8



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
    // Plane Graphics
    CONNECTION(DIR_SELECT_n, "J1", 10)
    CONNECTION(PH4, "J1", 9)

    CONNECTION(DIR_SELECT_n, "J1", 2)
    CONNECTION(PH3, "J1", 1)

    CONNECTION(DIR_SELECT_n, "J1", 4)
    CONNECTION(PH2, "J1", 5)

    CONNECTION(DIR_SELECT_n, "J1", 12)
    CONNECTION(PH1, "J1", 13)

    CONNECTION(GND, "DSW2", 1)
    CONNECTION(VCC, "DSW2", 2)
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    CONNECTION("VIDEO", 3, "L1", 15)
    CONNECTION("VIDEO", 4, "E1", 10)

    CONNECTION("VIDEO", Video::HBLANK_PIN, HSYNC)
    CONNECTION("VIDEO", Video::VBLANK_PIN, VSYNC)


CIRCUIT_LAYOUT_END
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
